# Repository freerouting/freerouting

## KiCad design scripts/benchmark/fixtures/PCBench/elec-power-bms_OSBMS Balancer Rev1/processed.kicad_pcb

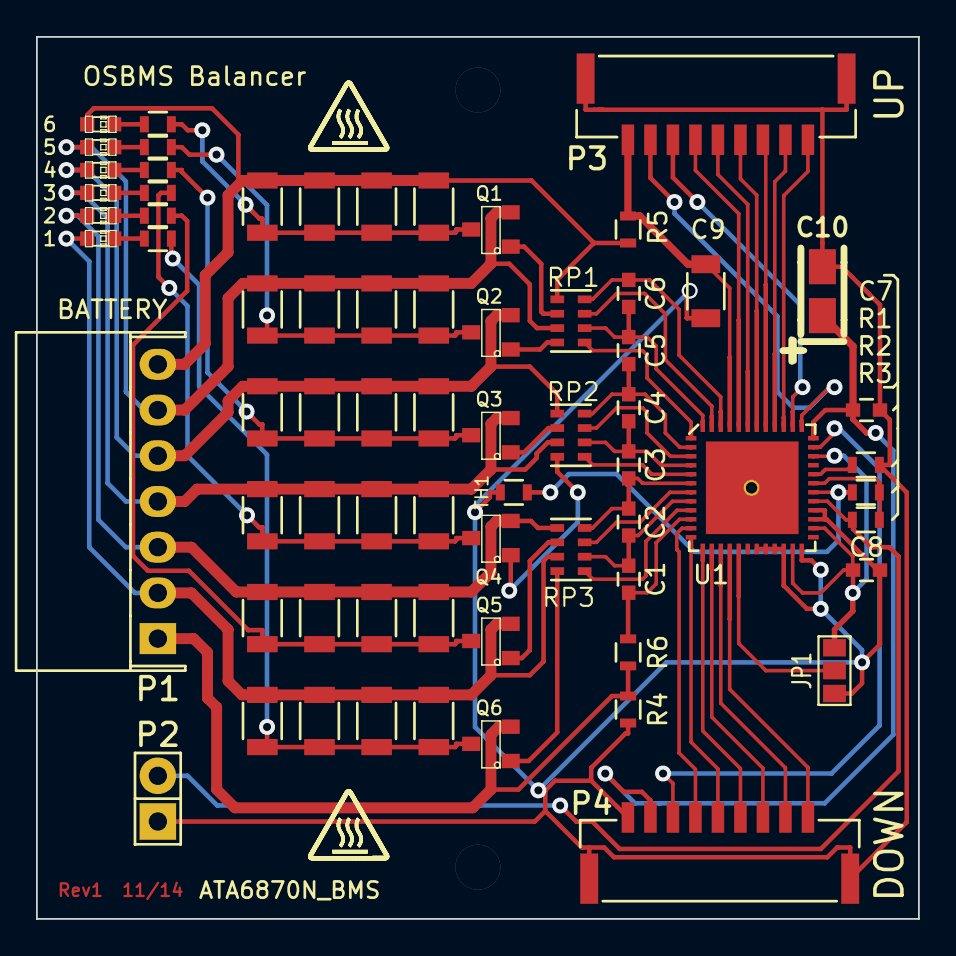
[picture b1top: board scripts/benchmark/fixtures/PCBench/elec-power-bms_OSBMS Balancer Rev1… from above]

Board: 2 copper layers, 49.0 x 49.0 mm, 74 parts (1 on the bottom side), 63 nets.

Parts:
28 mil Id via: via; 35-Od-28mil-Id-via
C1, C2, C3, C4, C5, C6, C7, C8: 100nF; C_0603
C9: 10uF PolC; C_1206
C10: 33uF PolC; TantalC_SizeA_EIA-3216_Reflow
D1, D2, D3, D4, D5, D6: LED; LED-0603
JP1: JUMPER3; GS3
MH: MountingHole_2-5mm_RevA_Date21Jun2010; MountingHole_2-5mm
MH_2: MountingHole_2-5mm_RevA_Date21Jun2010; MountingHole_2-5mm
P1: CONN_01X07; Shrouded_Header_Angled_1x07
P2: EXT-TMP; Pin_Header_Straight_1x02
P3, P4: CONN_01X09; Connector_SMD_GH_SIDECONN_1X9_1.25MM_45515711ND
P5: CONN_01X01; 1Pin
Q1, Q2, Q3, Q4, Q5, Q6: BSS138; SOT-23
R1: 121KΩ; R_0603
R2, R3: 10KΩ; R_0603
R4, R5: 10Ω; R_0603
R6: 1K; R_0603
R7, R8, R9, R10, R11, R12: 100Ω; R_0603
R13, R20, R21, R22, R23, R24, R25, R26, R27, R28, R29, R30, R31, R32, R33, R34, R35, R36, R37, R38, R39, R40, R41, R42: 82.5Ω; R_1206
RP1, RP2, RP3: 1K_PACK; R_Cat16-4
TH1: THERMISTOR; R_0603
U1: ATA6870N_BMS; QFN-48-1EP-refined
danger_hot_small: danger_hot_small
danger_hot_small_2: danger_hot_small

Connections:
+3.3V: C7.1, C10.1, P4.2, U1.36
+BATT: C9.1, P3.9, R5.1, U1.45
/DISCH1: RP3.5, U1.9
/DISCH2: RP3.7, U1.7
/DISCH3: RP2.5, U1.5
/DISCH4: RP2.7, U1.3
/DISCH5: RP1.5, U1.1
/DISCH6: RP1.7, U1.47
GND: C7.2, C8.2, C9.2, C10.2, JP1.3, P2.1, P4.1, R1.1, R4.1, TH1.2, U1.19, U1.20, U1.21, U1.22, U1.24, U1.27, U1.28
unnamed: C1.1, C2.2, RP3.6, U1.8
unnamed: C1.2, R6.1, U1.10
unnamed: C2.1, C3.2, RP3.8, U1.6
unnamed: C3.1, C4.2, RP2.6, U1.4
unnamed: C4.1, C5.2, RP2.8, U1.2
unnamed: C5.1, C6.2, RP1.6, U1.48
unnamed: C6.1, RP1.8, U1.46
unnamed: C8.1, JP1.1, U1.23, U1.26, U1.34
unnamed: D1.1, P1.7, R5.2, R20.1, R21.1, R22.1, R23.1, RP1.1
unnamed: D1.2, R12.2
unnamed: D2.1, P1.6, Q1.2, R24.1, R25.1, R26.1, R27.1, RP1.3
unnamed: D2.2, R11.2
unnamed: D3.1, P1.5, Q2.2, R28.1, R29.1, R30.1, R31.1, RP2.1
unnamed: D3.2, R10.2
unnamed: D4.1, P1.4, Q3.2, R13.1, R32.1, R33.1, R34.1, RP2.3
unnamed: D4.2, R9.2
unnamed: D5.1, P1.3, Q4.2, R35.1, R36.1, R37.1, R38.1, RP3.1
unnamed: D5.2, R8.2
unnamed: D6.1, P1.2, Q5.2, R39.1, R40.1, R41.1, R42.1, RP3.3
unnamed: D6.2, R7.2
unnamed: JP1.2, U1.17
unnamed: P1.1, Q6.2, R4.2, R6.2
unnamed: P2.2, R3.2, U1.29
unnamed: P3.1, U1.39
unnamed: P3.2, U1.40
unnamed: P3.3, U1.41
unnamed: P3.4, U1.42
unnamed: P3.5, U1.43
unnamed: P3.6, U1.44
unnamed: P3.7, U1.38
unnamed: P3.8, U1.37
unnamed: P4.3, U1.35
unnamed: P4.4, U1.11
unnamed: P4.5, U1.12
unnamed: P4.6, U1.13
unnamed: P4.7, U1.14
unnamed: P4.8, U1.15
unnamed: P4.9, U1.16
unnamed: Q1.1, RP1.2
unnamed: Q1.3, R12.1, R20.2, R21.2, R22.2, R23.2
unnamed: Q2.1, RP1.4
unnamed: Q2.3, R11.1, R24.2, R25.2, R26.2, R27.2
unnamed: Q3.1, RP2.2
unnamed: Q3.3, R10.1, R28.2, R29.2, R30.2, R31.2
unnamed: Q4.1, RP2.4
unnamed: Q4.3, R9.1, R13.2, R32.2, R33.2, R34.2
unnamed: Q5.1, RP3.2
unnamed: Q5.3, R8.1, R35.2, R36.2, R37.2, R38.2
unnamed: Q6.1, RP3.4
unnamed: Q6.3, R7.1, R39.2, R40.2, R41.2, R42.2
unnamed: R1.2, U1.32
unnamed: R2.1, R3.1, U1.31
unnamed: R2.2, TH1.1, U1.30
ThermalGnd: 28 mil Id via.1, U1.49

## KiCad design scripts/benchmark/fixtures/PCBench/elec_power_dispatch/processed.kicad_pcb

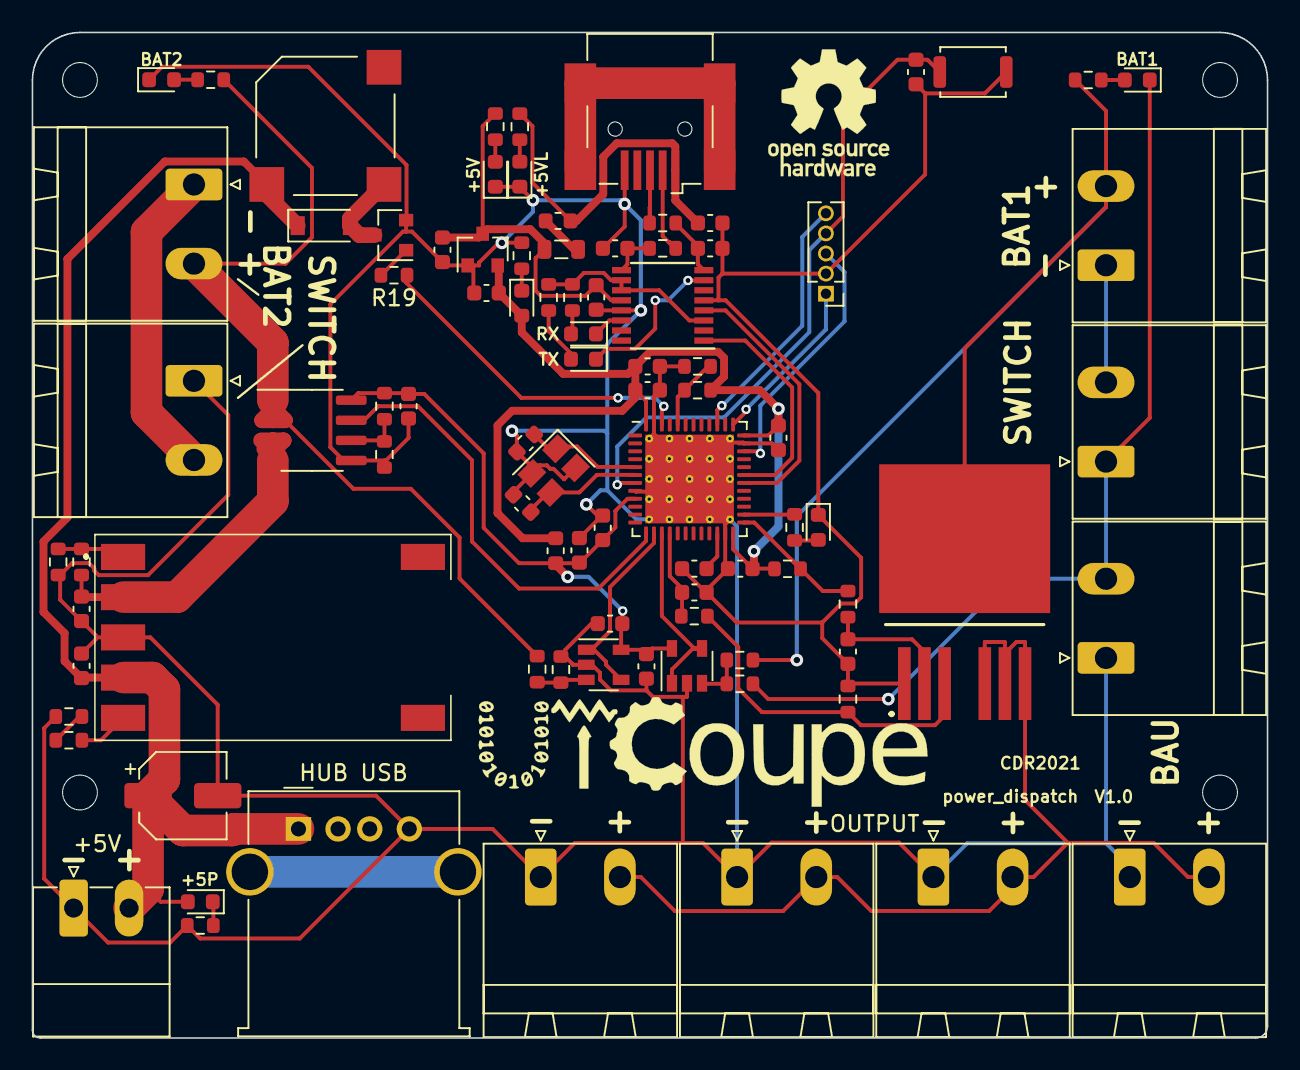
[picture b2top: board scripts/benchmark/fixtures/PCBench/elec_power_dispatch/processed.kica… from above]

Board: 2 copper layers, 78.0 x 63.5 mm, 95 parts (0 on the bottom side), 57 nets.

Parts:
BZ1: MLT-8530; MagneticBuzzer_Kobitone_254-EMB84Q-RO
C1, C4, C9, C13, C14, C15, C17, C18, C22, C24, C26: 100nF; C_0603_1608Metric
C2: 100uF/10V; CP_Elec_5x5.4
C3, C6, C12: 4u7; C_0603_1608Metric
C5, C7: 10uF; C_0603_1608Metric
C8: 220nF; C_0603_1608Metric
C10, C11: 12pF; C_0603_1608Metric
C16: 1u; C_0603_1608Metric
C19: 10nF; C_0603_1608Metric
C23, C25: 47pF; C_0603_1608Metric
D1, D2, D3, D4, D7, D9: red0603; LED_0603_1608Metric
D5, D6: blue0603; LED_0603_1608Metric
D8: 1N4148W; D_SOD-123
D10: green0603; LED_0603_1608Metric
F1: 100mA; Fuse_0603_1608Metric
FB1: 100 @ 100MHz; L_0805_2012Metric
H1, H2, H3, H4: MountingHole; MountingHole_2.2mm_M2
IC1: SRBH-06H1A1G; SRBH06H1A1G
IC2: BTS500251TADATMA2; IPB180N03S4L01
J1, J2, J3, J4, J5, J8, J9, J10, J11: Conn_01x02; PhoenixContact_MSTBA_2,5_2-G_1x02_P5.00mm_Horizontal
J6: USB_B_Mini; USB_Mini-B_Wuerth_65100516121_Horizontal
J7: Conn_01x05; PinHeader_1x05_P1.27mm_Vertical
J13: Conn_01x02; PhoenixContact_MC_1,5_2-G-3.5_1x02_P3.50mm_Horizontal
J15: USB_A; USB_A_Molex_67643_Horizontal
L1: 39nH; L_0603_1608Metric
LOGO1: Logo_Open_Hardware_Large; OSHW-Logo_7.5x8mm_SilkScreen
Q1: 2N7002E; SOT-23
R1, R10, R14, R24, R26: 3K3; R_0603_1608Metric
R2, R12: 4K7; R_0603_1608Metric
R3, R5, R6, R8, R25, R27, R28: 10K; R_0603_1608Metric
R4: 2K2; R_0603_1608Metric
R7, R9: 1K5; R_0603_1608Metric
R11, R13: 1K; R_0603_1608Metric
R15, R16: 27R; R_0603_1608Metric
R17, R20, R21: NC; R_0603_1608Metric
R18: 0R; R_0603_1608Metric
R19: 470R; R_0603_1608Metric
R22, R23: 270R; R_0603_1608Metric
SW1: SKRKAEE020; SW_Push_SPST_NO_Alps_SKRK
U1, U8: MCP6L01x-xOT; SOT-23-5
U2: STM32F411CEUx; QFN-48-1EP_7x7mm_P0.5mm_EP5.6x5.6mm_ThermalVias
U3: FT230XS; SSOP-16_3.9x4.9mm_P0.635mm
U4: ACS722xLCTR-10AB; SOIC-8_3.9x4.9mm_P1.27mm
U5: XC6206P332MR; SOT-23
Y1: 1C208000BC0K 8MHz; Crystal_SMD_3225-4Pin_3.2x2.5mm

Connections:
+3.3VA: C4.1, C9.1, C16.2, C17.2, C18.1, L1.2, R17.1, U1.5, U2.9, U4.8, U8.5
+3V3: C7.1, C12.2, C13.2, C14.2, C22.2, D7.2, L1.1, R20.2, R21.1, U2.24, U2.36, U2.48, U5.2
+5V: C5.1, C24.1, FB1.1, R24.1, U3.12, U5.3
+5VL: C3.1, F1.2, J6.1, R1.1
+5VP: BZ1.1, C2.1, C26.1, D3.2, D8.1, IC1.4, J13.2, J15.1
+12P: IC2.5, IC2.6, IC2.7, J8.2, J9.2, J10.2, J11.2
+12V: C1.1, IC1.2, R27.1, U4.3, U4.4
+12VA: J1.2, R3.1, R6.1, U4.1, U4.2
+BATT: IC2.4, J3.2, R5.1, R8.1
/TRIM: IC1.5, R10.2
BOOT0: R20.1, R25.2, U2.44
BUZZER: R19.1, U2.46
CBUS1: D5.1, U3.14
CBUS2: D6.1, U3.7
GND: C1.2, C2.2, C3.2, C4.2, C5.2, C6.2, C7.2, C8.2, C9.2, C10.1, C11.2, C12.1, C13.1, C14.1, C15.2, C16.1, C17.1, C18.2, C19.2, C22.1, C23.2, C24.2, C25.2, C26.2, D1.1, D2.1, D9.1, D10.1, IC1.3, IC2.1, J2.1, J5.1, J6.5, J7.2, J8.1, J9.1, J10.1, J11.1, J13.1, J15.4, Q1.2, R4.1, R7.2, R11.1, R13.1, R14.2, R18.2, R25.1, R28.2, SW1.2, U1.2, U2.8, U2.23, U2.35, U2.47, U2.49, U3.5, U3.13, U4.5, U5.1, U8.2, Y1.2, Y1.4
GNDBATT: J3.1, J4.2
HSE_IN: C10.2, U2.5, Y1.1
HSE_OUT: C11.1, U2.6, Y1.3
LED0: R26.1, U2.26
NRST: C15.1, J7.4, SW1.1, U2.7
unnamed: BZ1.2, D8.2, Q1.3
unnamed: C6.1, U2.22
unnamed: C8.1, IC2.2, R12.1
unnamed: C23.1, R15.2, U3.9
unnamed: C25.1, R16.2, U3.8
unnamed: D1.2, R1.2
unnamed: D2.2, R3.2
unnamed: D3.1, R4.2
unnamed: D4.1, J4.1, J5.2, R9.2
unnamed: D4.2, R5.2
unnamed: D5.2, R22.1
unnamed: D6.2, R23.1
unnamed: D7.1, R14.1
unnamed: D9.2, R24.2
unnamed: D10.2, R26.2
unnamed: F1.1, FB1.2
unnamed: IC1.1, R27.2, R28.1
unnamed: IC2.3, R2.1, R13.2
unnamed: J1.1, J2.2
unnamed: Q1.1, R19.2
unnamed: R6.2, R7.1, U1.3
unnamed: R8.2, R9.1, U8.3
unnamed: R10.1, R11.2
unnamed: R17.2, R18.1, U4.6
PWRCMD: R12.2, R21.2, U2.25
SWCLK: J7.1, U2.37
SWDIO: J7.3, U2.34
SWO: J7.5, U2.39
UART_RX: U2.31, U3.1
UART_TX: U2.30, U3.4
USB_D+: J6.3, R16.1
USB_D-: J6.2, R15.1
VCCIO: R22.2, R23.2, U3.3, U3.10, U3.11
VILOGIC: U2.13, U4.7
VIPOWER: C19.1, R2.2, U2.16
VVLOGIC: U1.1, U1.4, U2.14
VVPOWER: U2.15, U8.1, U8.4
